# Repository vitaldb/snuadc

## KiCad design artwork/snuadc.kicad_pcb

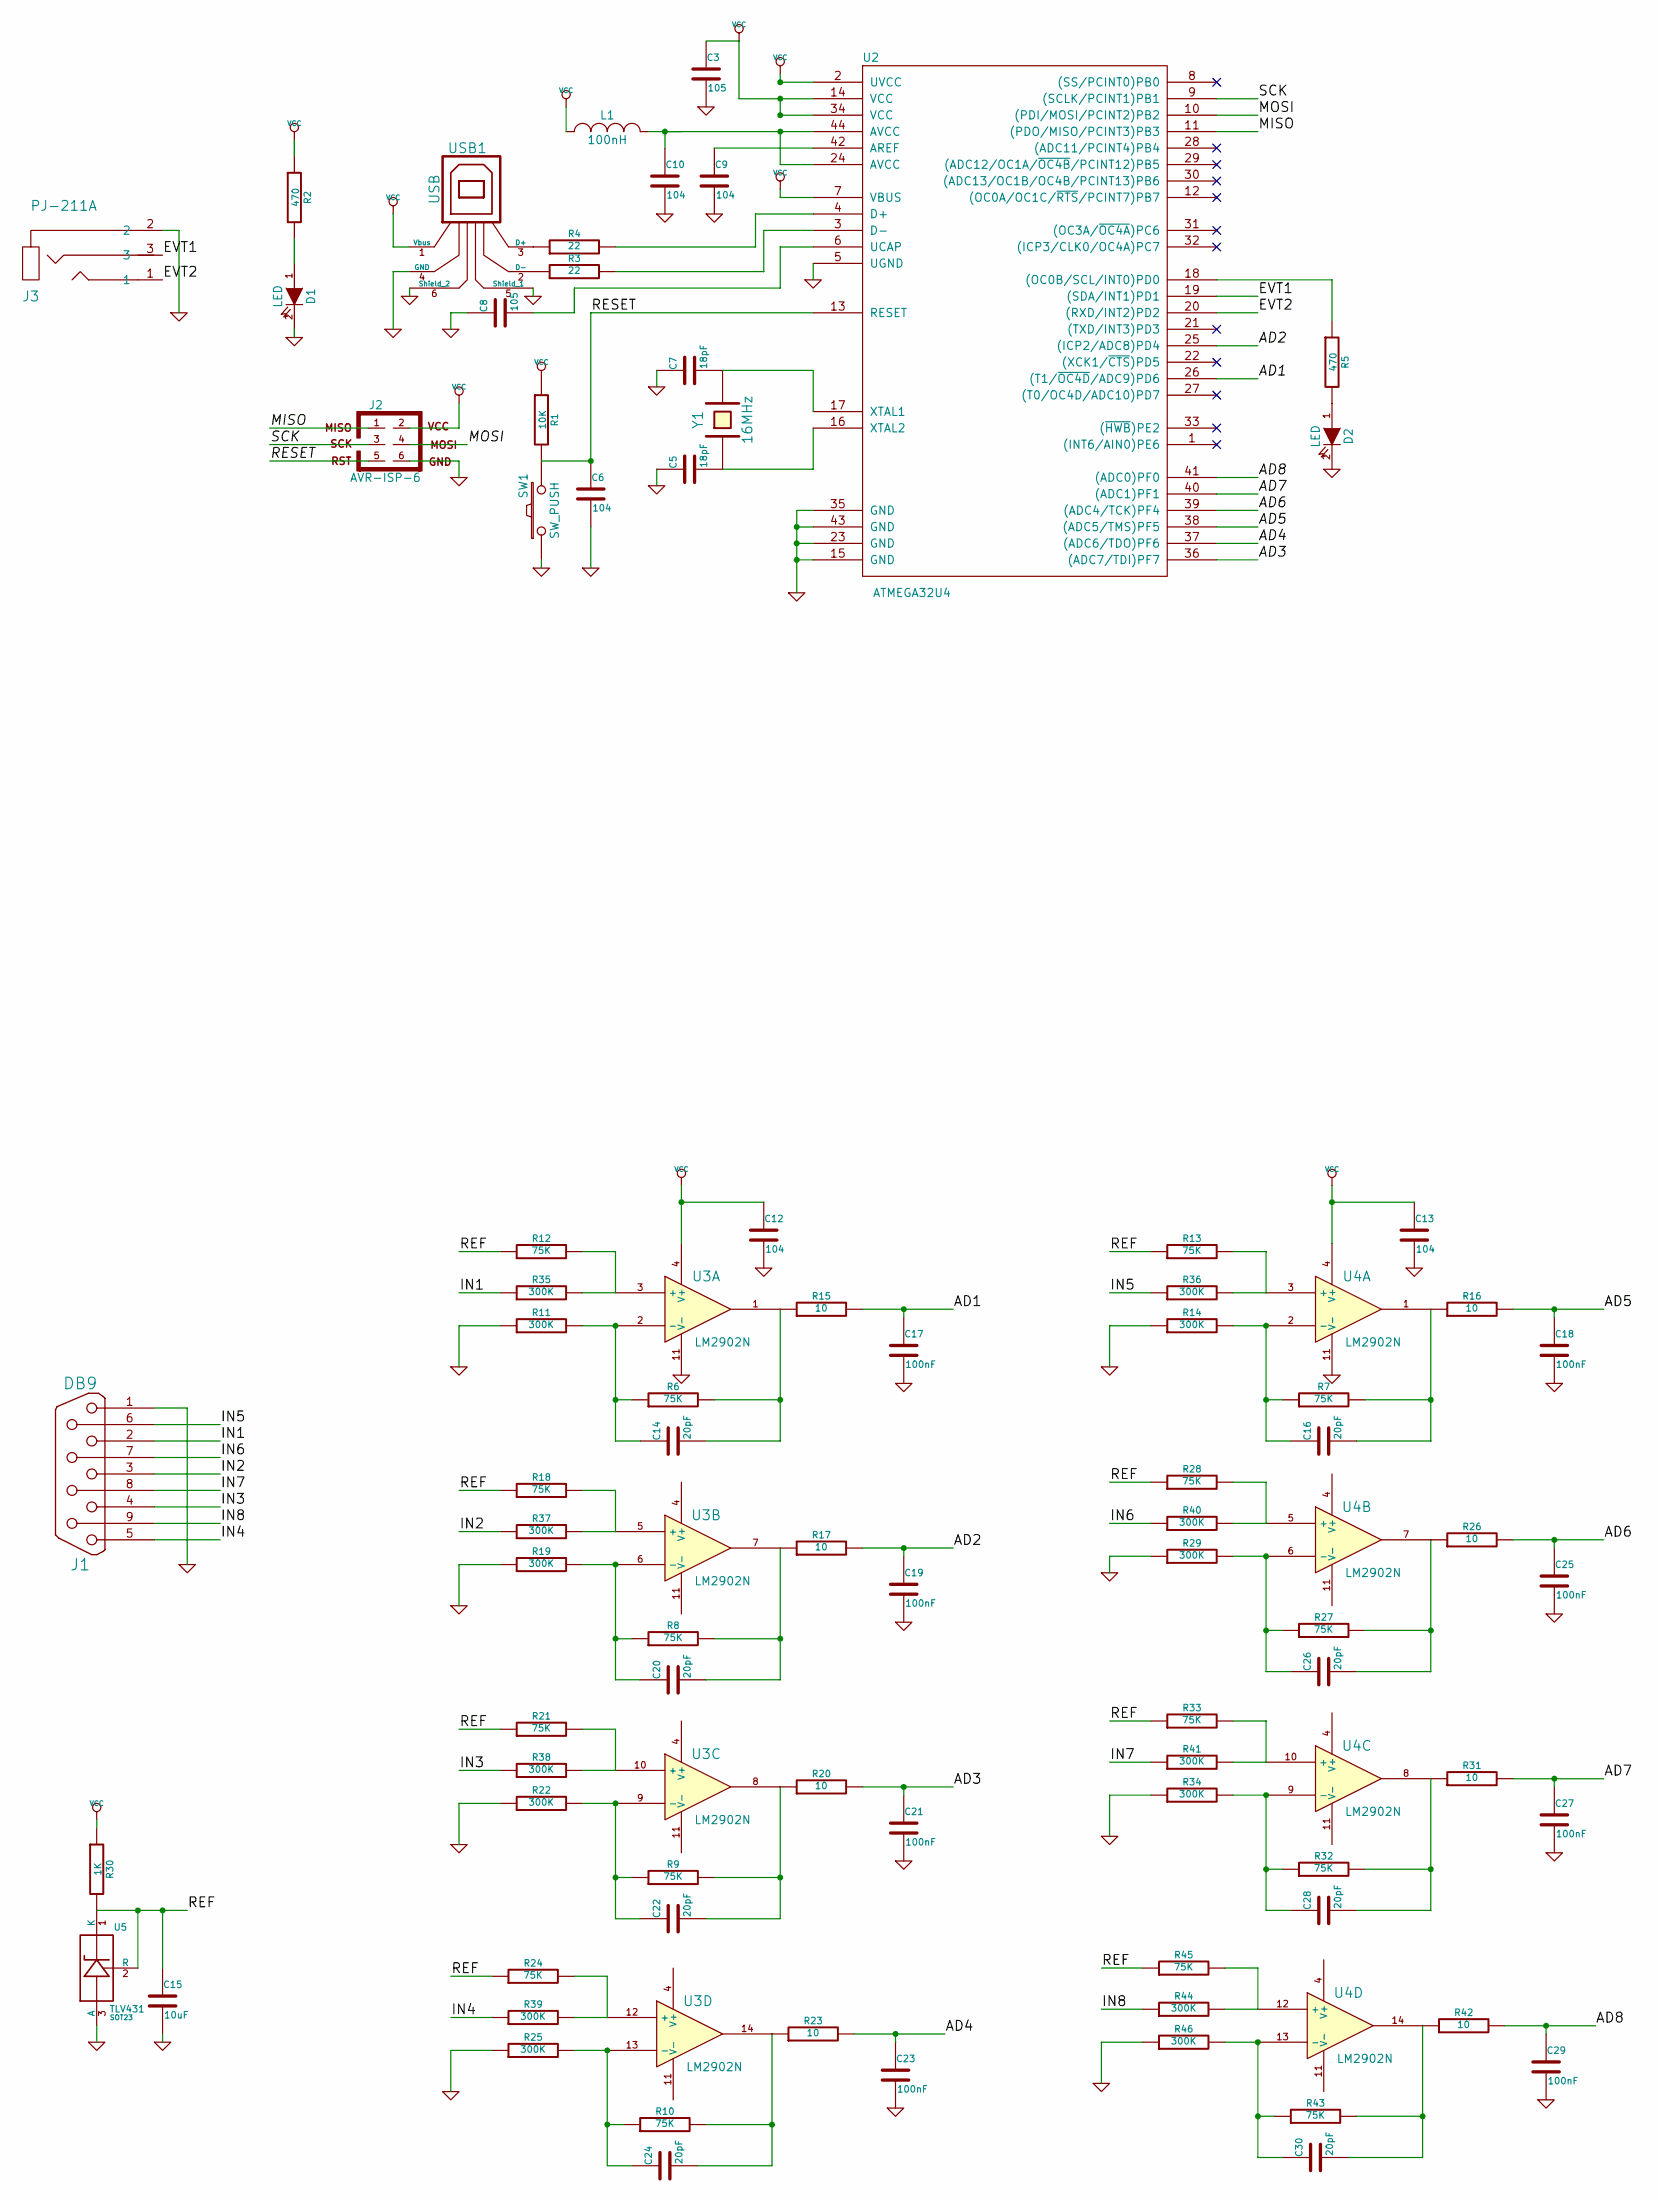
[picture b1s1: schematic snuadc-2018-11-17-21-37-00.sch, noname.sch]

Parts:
C3, C8: 105
C5, C7: 18pF
C6, C9, C10, C12, C13: 104
C14, C16, C20, C22, C24, C26, C28, C30: 20pF
C15: 10uF
C17, C18, C19, C21, C23, C25, C27, C29: 100nF
D1, D2: LED
J1: DB9
J2: AVR-ISP-6
J3: PJ-211A
L1: 100nH
R1: 10K
R2, R5: 470
R3, R4: 22
R6, R7, R8, R9, R10, R12, R13, R18, R21, R24, R27, R28, R32, R33, R43, R45: 75K
R11, R14, R19, R22, R25, R29, R34, R35, R36, R37, R38, R39, R40, R41, R44, R46: 300K
R15, R16, R17, R20, R23, R26, R31, R42: 10
R30: 1K
SW1: SW_PUSH
U2: ATMEGA32U4
U3, U4: LM2902N
U5: TLV431; SOT23
USB1: USB
Y1: 16MHz

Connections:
/AD1: C17.1, R15.2, U2.26 ((T1/~OC4D~/ADC9)PD6)
/AD2: C19.1, R17.2, U2.25 ((ICP2/ADC8)PD4)
/AD3: C21.1, R20.2, U2.36 ((ADC7/TDI)PF7)
/AD4: C23.1, R23.2, U2.37 ((ADC6/TDO)PF6)
/AD5: C18.1, R16.2, U2.38 ((ADC5/TMS)PF5)
/AD6: C25.1, R26.2, U2.39 ((ADC4/TCK)PF4)
/AD7: C27.1, R31.2, U2.40 ((ADC1)PF1)
/AD8: C29.1, R42.2, U2.41 ((ADC0)PF0)
/EVT1: J3.3, U2.19 ((SDA/INT1)PD1)
/EVT2: J3.1, U2.20 ((RXD/INT2)PD2)
/IN1: J1.2, R35.1
/IN2: J1.3, R37.1
/IN3: J1.4, R38.1
/IN4: J1.5, R39.1
/IN5: J1.6, R36.1
/IN6: J1.7, R40.1
/IN7: J1.8, R41.1
/IN8: J1.9, R44.1
/MISO: J2.1, U2.11 ((PDO/MISO/PCINT3)PB3)
/MOSI: J2.4, U2.10 ((PDI/MOSI/PCINT2)PB2)
/REF: C15.1, R12.1, R13.1, R18.1, R21.1, R24.1, R28.1, R30.2, R33.1, R45.1, U5.1 (K), U5.2 (R)
/RESET: C6.1, J2.5, R1.2, SW1.2, U2.13 (RESET)
/SCK: J2.3, U2.9 ((SCLK/PCINT1)PB1)
GND: C3.2, C5.1, C6.2, C7.1, C8.1, C9.2, C10.2, C12.2, C13.2, C15.2, C17.2, C18.2, C19.2, C21.2, C23.2, C25.2, C27.2, C29.2, D1.2 (K), D2.2 (K), J1.1, J2.6, J3.2, R11.1, R14.1, R19.1, R22.1, R25.1, R29.1, R34.1, R46.1, SW1.1, U2.5 (UGND), U2.15 (GND), U2.23 (GND), U2.35 (GND), U2.43 (GND), U3.11 (V-), U4.11 (V-), U5.3 (A), USB1.4 (GND), USB1.5 (Shield_1), USB1.6 (Shield_2)
unnamed: C20.2, R8.2, R17.1, U3.7
unnamed: C20.1, R8.1, R19.2, U3.6 (-)
unnamed: R28.2, R40.2, U4.5 (+)
unnamed: C26.1, R27.1, R29.2, U4.6 (-)
unnamed: R13.2, R36.2, U4.3 (+)
unnamed: C16.2, R7.2, R16.1, U4.1
unnamed: C26.2, R26.1, R27.2, U4.7
unnamed: C16.1, R7.1, R14.2, U4.2 (-)
unnamed: R18.2, R37.2, U3.5 (+)
unnamed: C22.2, R9.2, R20.1, U3.8
unnamed: R33.2, R41.2, U4.10 (+)
unnamed: C22.1, R9.1, R22.2, U3.9 (-)
unnamed: C28.1, R32.1, R34.2, U4.9 (-)
unnamed: C28.2, R31.1, R32.2, U4.8
unnamed: R21.2, R38.2, U3.10 (+)
unnamed: C7.2, U2.17 (XTAL1), Y1.2
unnamed: C14.2, R6.2, R15.1, U3.1
unnamed: R12.2, R35.2, U3.3 (+)
unnamed: C14.1, R6.1, R11.2, U3.2 (-)
unnamed: D1.1 (A), R2.2
unnamed: R4.2, U2.4 (D+)
unnamed: C5.2, U2.16 (XTAL2), Y1.1
unnamed: R3.2, U2.3 (D-)
unnamed: C8.2, U2.6 (UCAP)
unnamed: R44.2, R45.2, U4.12 (+)
unnamed: C30.1, R43.1, R46.2, U4.13 (-)
unnamed: C30.2, R42.1, R43.2, U4.14
unnamed: R24.2, R39.2, U3.12 (+)
unnamed: C24.1, R10.1, R25.2, U3.13 (-)
unnamed: C24.2, R10.2, R23.1, U3.14
unnamed: C9.1, U2.42 (AREF)
unnamed: C10.1, L1.2, U2.24 (AVCC), U2.44 (AVCC)
unnamed: R5.1, U2.18 ((OC0B/SCL/INT0)PD0)
unnamed: D2.1 (A), R5.2
unnamed: R3.1, USB1.2 (D-)
unnamed: R4.1, USB1.3 (D+)
VCC: C3.1, C12.1, C13.1, J2.2, L1.1, R1.1, R2.1, R30.1, U2.2 (UVCC), U2.7 (VBUS), U2.14 (VCC), U2.34 (VCC), U3.4 (V+), U4.4 (V+), USB1.1 (Vbus)

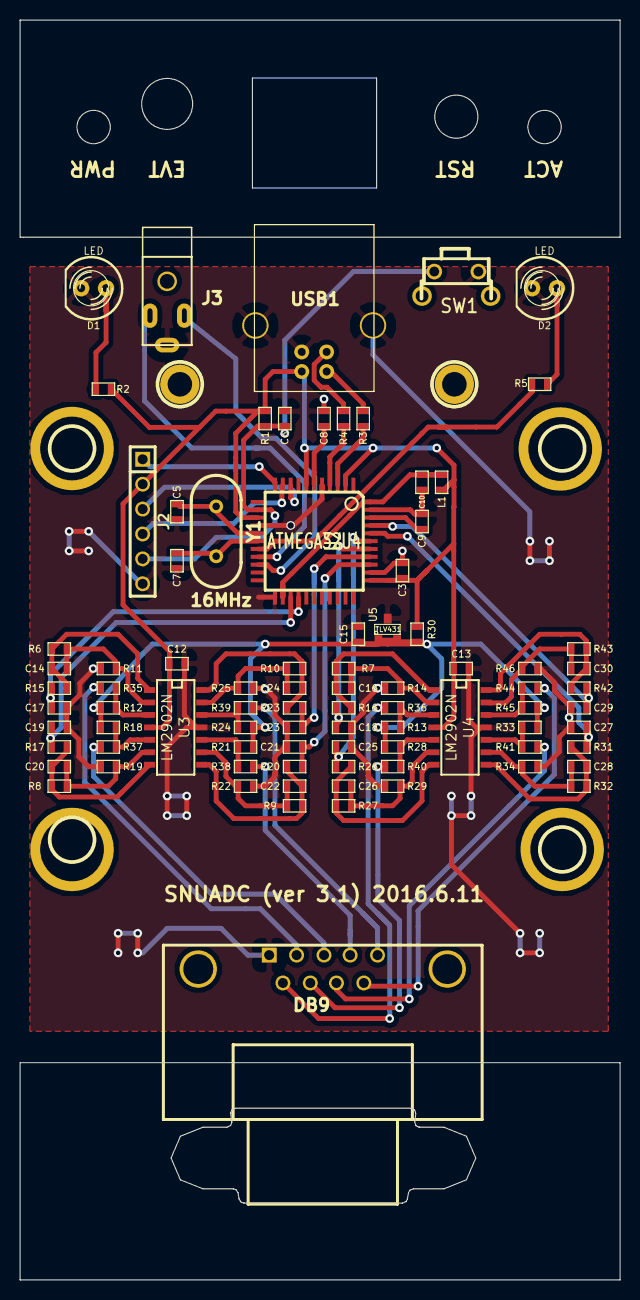
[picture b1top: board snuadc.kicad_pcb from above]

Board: 2 copper layers, 61.2 x 128.5 mm, 84 parts (0 on the bottom side), 53 nets.

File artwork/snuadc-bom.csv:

Id,Designator,Package,Quantity,Designation,Supplier and ref
1,U2,TQFP44,1,ATMEGA32U4,http://eleparts.co.kr/EPXBVLJA
2,"U4,U3",SO14E,2,LM2902N,
3,Y1,HC-49V,1,16MHz,http://eleparts.co.kr/EPXFK6RT
4,DB9,DB9MC,1,DB9,http://eleparts.co.kr/EPX348B6
5,SW1,MINIBUTVERT,1,SW1,http://eleparts.co.kr/EPXGHL7P
6,U5,SOT23,1,TLV431,http://eleparts.co.kr/EPXFUWTU
7,J3,PJ211A,1,PJ211A,http://eleparts.co.kr/EPX33TCT
8,USB1,USB_B,1,USB_B,
9,L1,SM0603,1,100nH,
10,J2,PIN_ARRAY_6X1,1,AVR-ISP-6,
11,D1,LED-3MM,2,LED (green),
12,D2,LED-3MM,2,LED (red),
13,"R15,R26,R42,R16,R17,R31,R20,R23",SM0603,8,10,
14,"R21,R13,R45,R18,R27,R28,R43,R6,R12,R10,R9,R8,R24,R7,R32,R33",SM0603,16,75K,
15,"R14,R25,R35,R37,R41,R46,R36,R22,R38,R29,R39,R44,R19,R11,R34,R40",SM0603,16,300K,
16,"R3,R4",SM0603,2,22,
17,"R5,R2",SM0603,2,470,
18,R30,SM0603,1,1K,
19,R1,SM0603,1,10K,
20,"C22,C20,C16,C26,C24,C14,C28,C30",SM0603,8,20pF,
21,"C7,C5",SM0603,2,18pF,
22,"C12,C6,C10,C9,C13,C17,C21,C19,C18,C25,C23,C27,C29",SM0603,13,100nF,104
23,"C3,C8",SM0603,1,1uF,105
24,C15,SM0603,1,10uF,

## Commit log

2018-11-22 initial
